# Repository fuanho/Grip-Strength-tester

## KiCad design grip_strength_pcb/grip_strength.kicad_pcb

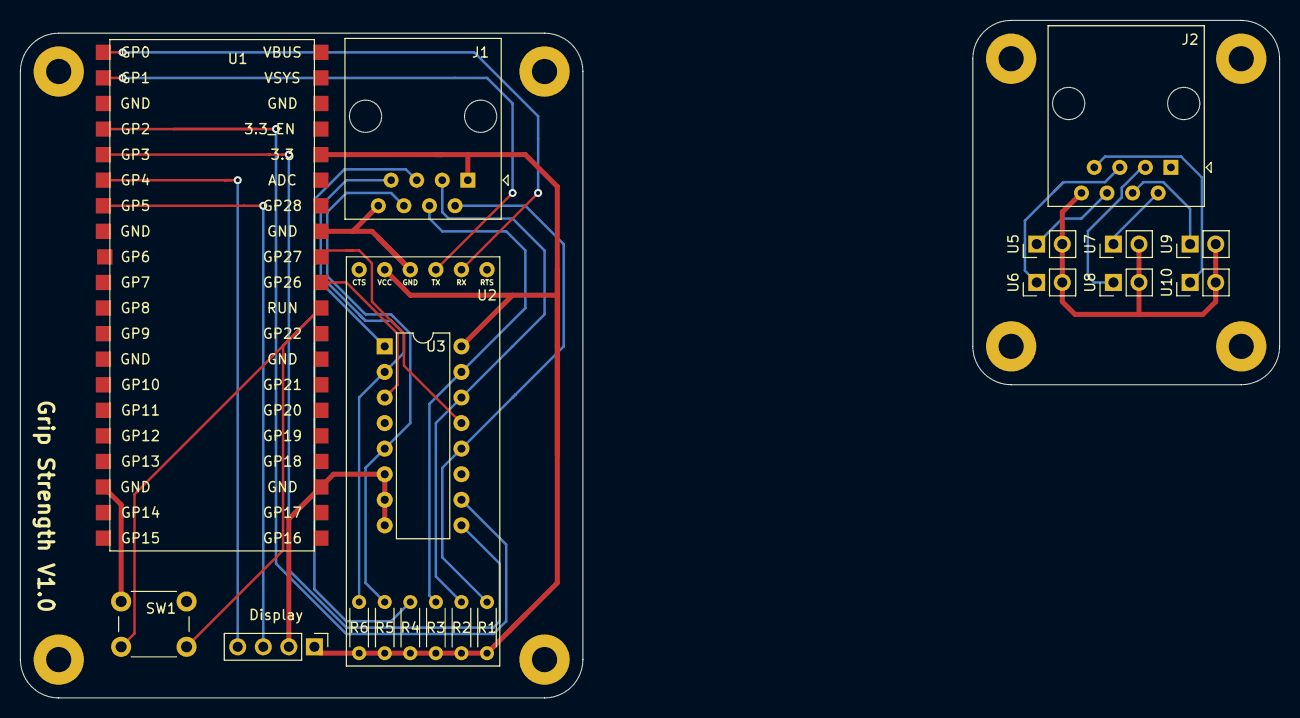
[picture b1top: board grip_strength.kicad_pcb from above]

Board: 2 copper layers, 125.1 x 67.3 mm, 27 parts (0 on the bottom side), 23 nets.

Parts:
H1, H2, H3, H4, H5, H6, H7, H8: MountingHole; MountingHole_2.5mm_Pad
J1, J2: RJ45; RJ45_Amphenol_54602-x08_Horizontal
R1, R2, R3, R4, R5, R6: R; R_Axial_DIN0204_L3.6mm_D1.6mm_P5.08mm_Horizontal
SW1: SW_Push; SW_PUSH_6mm_H5mm
U1: PICO_RP2040; pico_rp2040_sip
U2: bt_rn42
U3: 4052; DIP-16_W7.62mm
U4: ssd1306-128x64; PinHeader_1x04_P2.54mm_Vertical
U5, U6, U7, U8, U9, U10: 40PC015G; PinHeader_1x02_P2.54mm_Vertical

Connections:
GNDREF: J1.8, J2.8, SW1.2, U1.3, U1.13, U1.18, U1.23, U1.28, U1.33, U1.38, U2.4, U3.6, U3.7, U3.8, U4.2, U5.2, U6.2, U7.2, U8.2, U9.2, U10.2
unnamed: J1.2, R1.2, U3.12
unnamed: J1.3, R2.2, U3.14
unnamed: J1.4, R3.2, U3.15
unnamed: J1.5, R4.2, U3.1
unnamed: J1.6, R5.2, U3.5
unnamed: J1.7, R6.2, U3.2
unnamed: J2.2, U7.1
unnamed: J2.3, U8.1
unnamed: J2.4, U9.1
unnamed: J2.5, U6.1
unnamed: J2.6, U5.1
unnamed: J2.7, U10.1
unnamed: SW1.1, U1.30
unnamed: U1.1, U2.2
unnamed: U1.2, U2.3
unnamed: U1.4, U3.10
unnamed: U1.5, U3.9
unnamed: U1.6, U4.4
unnamed: U1.7, U4.3
unnamed: U1.31, U3.3
unnamed: U1.32, U3.13
VCC: J1.1, J2.1, R1.1, R2.1, R3.1, R4.1, R5.1, R6.1, U1.36, U2.5, U3.16, U4.1

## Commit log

2021-10-07 first upload
